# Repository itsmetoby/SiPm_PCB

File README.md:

View this project on [CADLAB.io](https://cadlab.io/project/28530). 

# SiPm_PCB

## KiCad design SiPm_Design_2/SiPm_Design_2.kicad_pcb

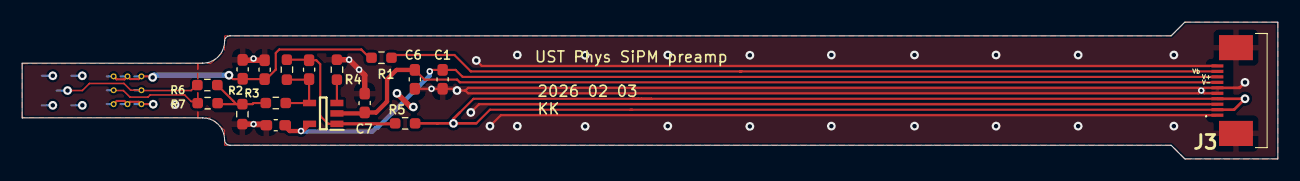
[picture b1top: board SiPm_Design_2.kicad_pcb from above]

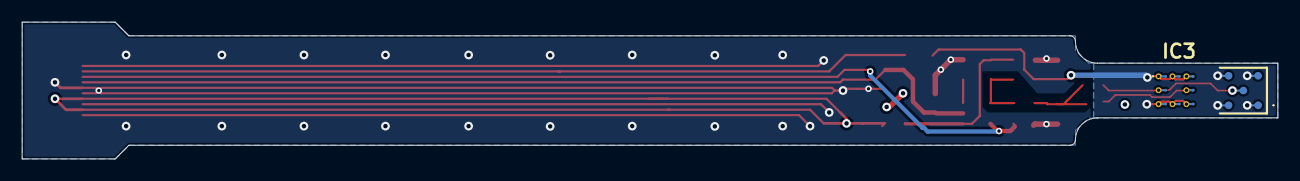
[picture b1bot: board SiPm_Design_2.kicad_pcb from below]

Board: 2 copper layers, 114.8 x 12.5 mm, 19 parts (2 on the bottom side), 12 nets.

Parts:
C1, C6: 100n; C_0603_1608Metric_Pad1.08x0.95mm_HandSolder
C2, C5, C7: 10n; C_0603_1608Metric_Pad1.08x0.95mm_HandSolder
C3: 1n; C_0603_1608Metric_Pad1.08x0.95mm_HandSolder
Cf1: 10p; C_0603_1608Metric_Pad1.08x0.95mm_HandSolder
IC1: OPA354AIDBVTG4; SOT95P280X145-5N
IC2: AFBR-S4N44P014M; AFBRS4N44P014M
IC3: MICROFJ-30035-TSV-TR; MICROFJ30035TSVTR
J3: 1-1734839-0; 117348390
R1: 1k; R_0603_1608Metric_Pad0.98x0.95mm_HandSolder
R2, R5: 50; R_0603_1608Metric_Pad0.98x0.95mm_HandSolder
R3, R4: 20; R_0603_1608Metric_Pad0.98x0.95mm_HandSolder
R6, R7: 0; R_0603_1608Metric_Pad0.98x0.95mm_HandSolder
Rf1: 200; R_0603_1608Metric_Pad0.98x0.95mm_HandSolder

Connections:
0: C1.2, C2.2, C3.2, C5.2, C6.1, C7.1, J3.1, J3.3, J3.5, J3.6, J3.10, J3.MP1, J3.MP2, R2.2, R4.2
+2V5: C1.1, C5.1, IC1.5 (V+), J3.8
-2V5: C6.2, C7.2, IC1.2 (V-), J3.7
/Bias: C2.1, C3.1, IC2.A1 (CATHODE_1), IC2.A3 (CATHODE_2), IC2.C1 (CATHODE_3), IC2.C3 (CATHODE_4), IC3.A1 (CATHODE_1), IC3.A2 (NO_CONNECT_1), IC3.A3 (NO_CONNECT_2), IC3.C1 (NO_CONNECT_3), IC3.C2 (NO_CONNECT_4), IC3.C3 (CATHODE_2), R1.1
/IN_n: Cf1.1, IC1.4 (-IN), R3.1, Rf1.1
/IN_p: IC1.3 (+IN), R4.1
/Vout: Cf1.2, IC1.1 (OUT), R5.2, Rf1.2
/anode: IC2.B2 (ANODE), IC3.B1 (ANODE), R6.1
/fastA: IC3.B3 (FAST_OUTPUT), R7.2
/in: R2.1, R3.2, R6.2, R7.1
V_bias: J3.9, R1.2
out: J3.2, J3.4, R5.1

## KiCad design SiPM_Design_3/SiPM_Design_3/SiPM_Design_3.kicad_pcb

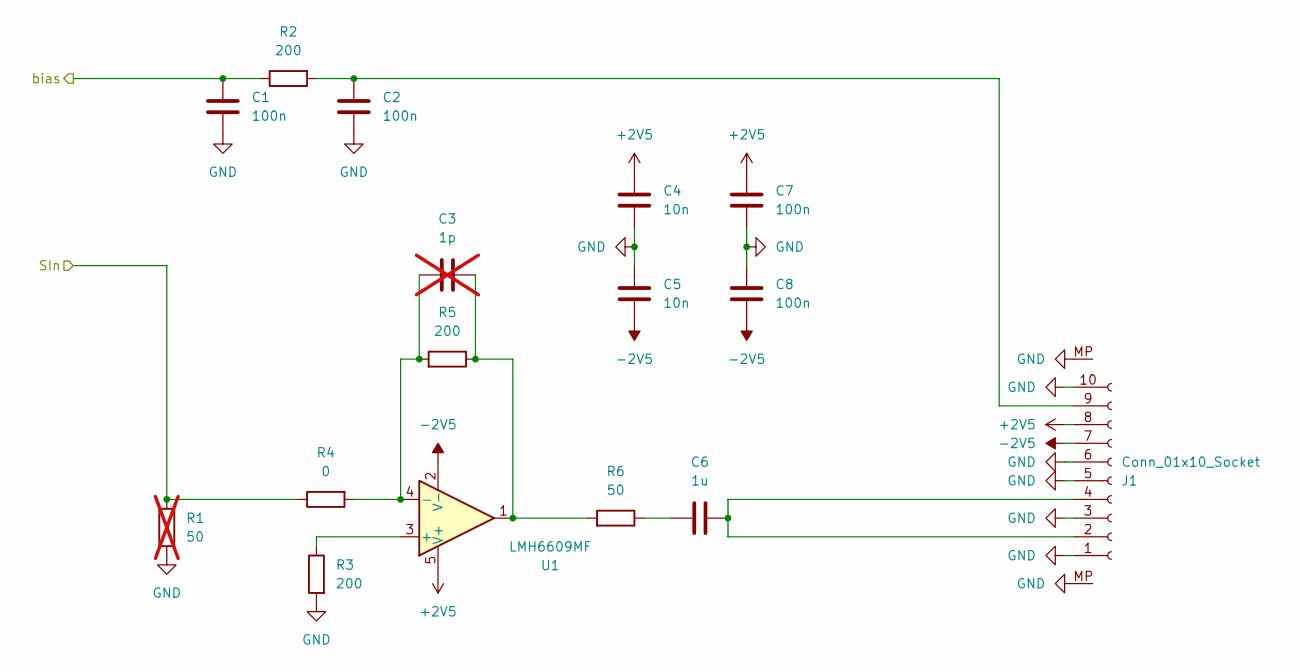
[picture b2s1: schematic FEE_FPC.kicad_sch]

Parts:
C1, C2, C7, C8: 100n; C_0603_1608Metric
C3: 1p; C_0402_1005Metric; not fitted
C4, C5: 10n; C_0402_1005Metric
C6: 1u; C_0603_1608Metric
J1: Conn_01x10_Socket; Hirose_FH12-10S-0.5SH_1x10-1MP_P0.50mm_Horizontal
R1: 50; R_0603_1608Metric; not fitted
R2, R3, R5: 200; R_0603_1608Metric
R4: 0; R_0603_1608Metric
R6: 50; R_0603_1608Metric
U1: LMH6609MF; SOT-23-5

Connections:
+2V5: C4.1, C7.1, J1.8, U1.5 (V+); also elsewhere on the board
-2V5: C5.2, C8.2, J1.7, U1.2 (V-); also elsewhere on the board
/FEE_FPC_1/SIn: R1.2, R4.2; also elsewhere on the board
/SiPM_onsemi/C: C1.1, R2.2; also elsewhere on the board
GND: C1.2, C2.2, C4.2, C5.1, C7.2, C8.1, J1.1, J1.3, J1.5, J1.6, J1.10, J1.MP, R1.1, R3.1; also elsewhere on the board
unnamed: C3.2, R5.2, R6.1, U1.1
unnamed: C6.1, R6.2
unnamed: C6.2, J1.2, J1.4
unnamed: C2.1, J1.9, R2.1
unnamed: R3.2, U1.3 (+)
unnamed: C3.1, R4.1, R5.1, U1.4 (-)

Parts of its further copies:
C9, C10, C15, C16: 100n; C_0603_1608Metric
C11: 1p; C_0402_1005Metric; not fitted
C12, C13: 10n; C_0402_1005Metric
C14: 1u; C_0603_1608Metric
J2: Conn_01x10_Socket; Hirose_FH12-10S-0.5SH_1x10-1MP_P0.50mm_Horizontal
R7: 50; R_0603_1608Metric; not fitted
R8, R9, R11: 200; R_0603_1608Metric
R10: 0; R_0603_1608Metric
R12: 50; R_0603_1608Metric
U2: LMH6609MF; SOT-23-5

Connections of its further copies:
+2V5: C12.1, C15.1, J2.8, U2.5 (V+); also elsewhere on the board
-2V5: C13.2, C16.2, J2.7, U2.2 (V-); also elsewhere on the board
/SiPM_broadcom/A: R7.2, R10.2; also elsewhere on the board
/SiPM_broadcom/C: C9.1, R8.2; also elsewhere on the board
GND: C9.2, C10.2, C12.2, C13.1, C15.2, C16.1, J2.1, J2.3, J2.5, J2.6, J2.10, J2.MP, R7.1, R9.1; also elsewhere on the board
unnamed: C11.2, R11.2, R12.1, U2.1
unnamed: C14.1, R12.2
unnamed: C14.2, J2.2, J2.4
unnamed: C10.1, J2.9, R8.1
unnamed: R9.2, U2.3 (+)
unnamed: C11.1, R10.1, R11.1, U2.4 (-)

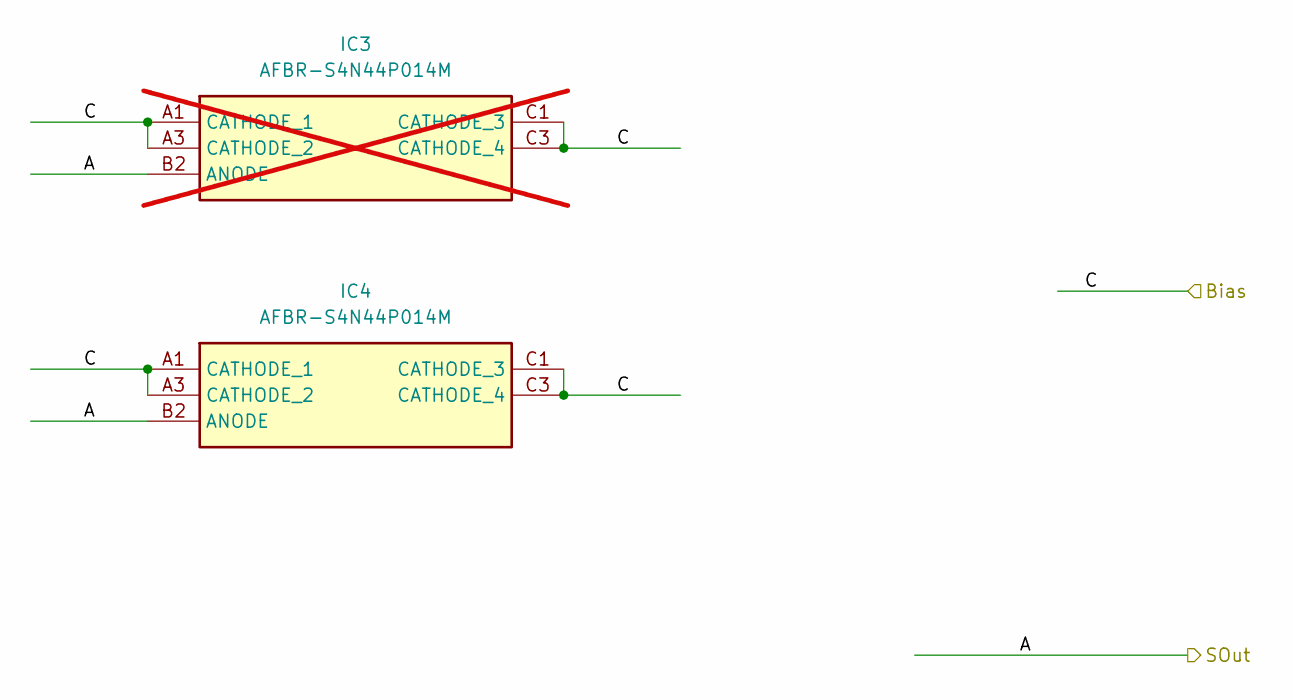
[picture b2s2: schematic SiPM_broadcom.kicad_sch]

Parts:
IC3: AFBR-S4N44P014M; AFBRS4N44P014M_offset; Manufacturer_Part_Number AFBR-S4N44P014M; Mouser Part Number 630-AFBR-S4N44P014M; not fitted
IC4: AFBR-S4N44P014M; AFBRS4N44P014M_offset; Manufacturer_Part_Number AFBR-S4N44P014M; Mouser Part Number 630-AFBR-S4N44P014M

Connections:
/SiPM_broadcom/A: IC3.B2 (ANODE), IC4.B2 (ANODE); also elsewhere on the board
/SiPM_broadcom/C: IC3.A1 (CATHODE_1), IC3.A3 (CATHODE_2), IC3.C1 (CATHODE_3), IC3.C3 (CATHODE_4), IC4.A1 (CATHODE_1), IC4.A3 (CATHODE_2), IC4.C1 (CATHODE_3), IC4.C3 (CATHODE_4); also elsewhere on the board

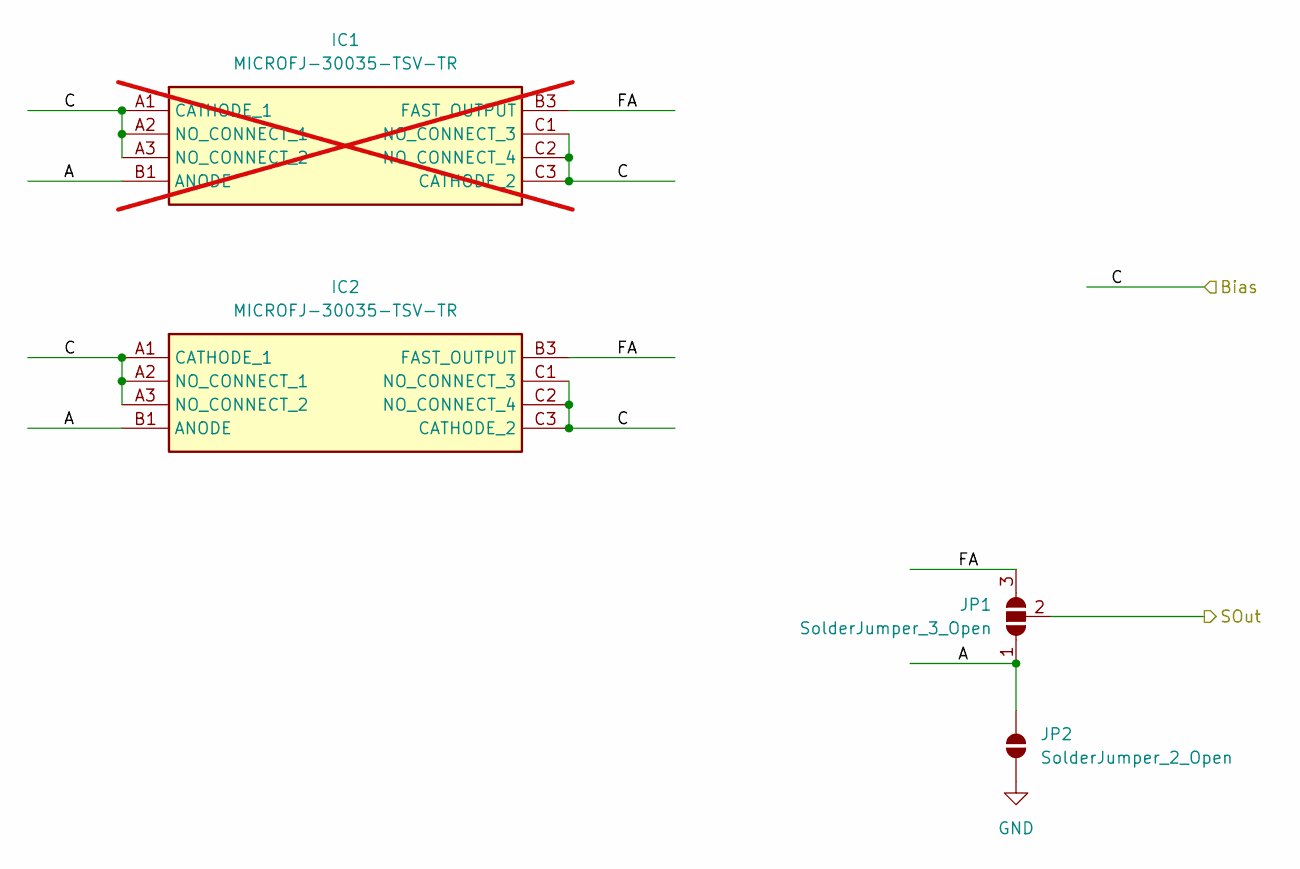
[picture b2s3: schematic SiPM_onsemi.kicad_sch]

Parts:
IC1: MICROFJ-30035-TSV-TR; MICROFJ30035TSVTR_offset; Manufacturer_Part_Number MICROFJ-30035-TSV-TR; Mouser Part Number 863-MFJ30035TSVTR; not fitted
IC2: MICROFJ-30035-TSV-TR; MICROFJ30035TSVTR_offset; Manufacturer_Part_Number MICROFJ-30035-TSV-TR; Mouser Part Number 863-MFJ30035TSVTR
JP1: SolderJumper_3_Open; SolderJumper-3_P1.3mm_Open_Pad1.0x1.5mm
JP2: SolderJumper_2_Open; SolderJumper-2_P1.3mm_Open_RoundedPad1.0x1.5mm

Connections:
/FEE_FPC_1/SIn: JP1.2 (C); also elsewhere on the board
/SiPM_onsemi/A: IC1.B1 (ANODE), IC2.B1 (ANODE), JP1.1 (A), JP2.2 (B)
/SiPM_onsemi/C: IC1.A1 (CATHODE_1), IC1.A2 (NO_CONNECT_1), IC1.A3 (NO_CONNECT_2), IC1.C1 (NO_CONNECT_3), IC1.C2 (NO_CONNECT_4), IC1.C3 (CATHODE_2), IC2.A1 (CATHODE_1), IC2.A2 (NO_CONNECT_1), IC2.A3 (NO_CONNECT_2), IC2.C1 (NO_CONNECT_3), IC2.C2 (NO_CONNECT_4), IC2.C3 (CATHODE_2); also elsewhere on the board
/SiPM_onsemi/FA: IC1.B3 (FAST_OUTPUT), IC2.B3 (FAST_OUTPUT), JP1.3 (B)
GND: JP2.1 (A); also elsewhere on the board

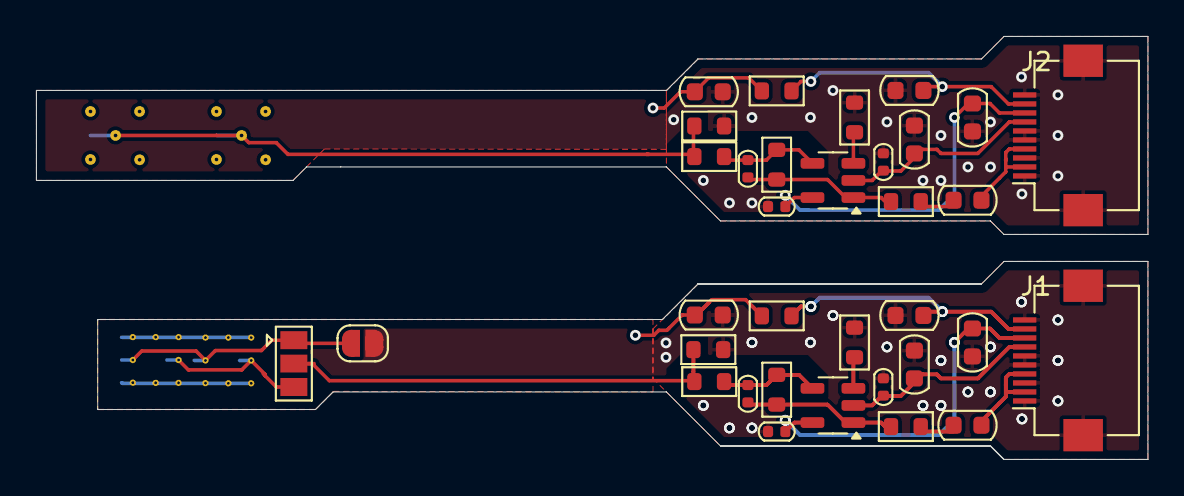
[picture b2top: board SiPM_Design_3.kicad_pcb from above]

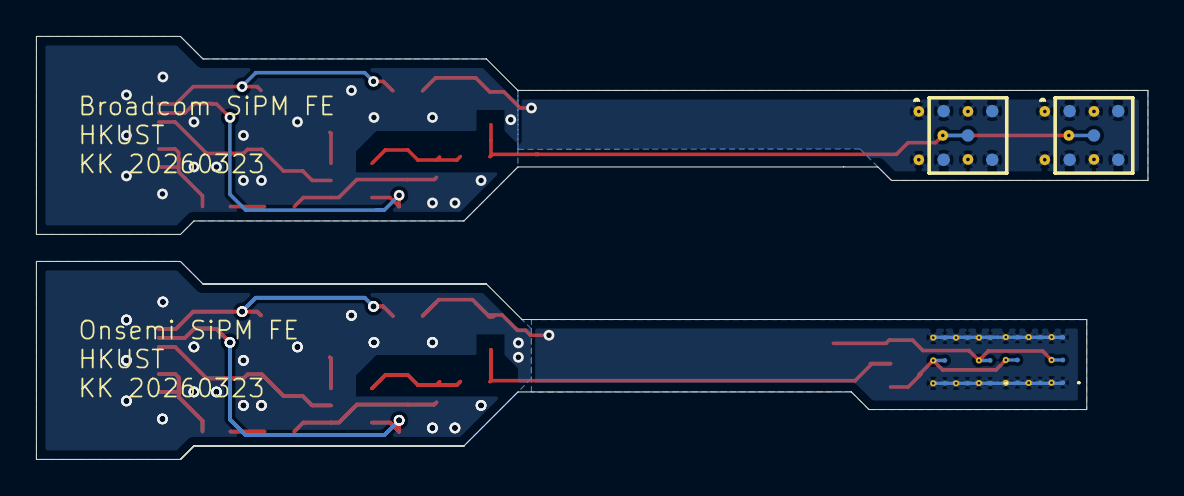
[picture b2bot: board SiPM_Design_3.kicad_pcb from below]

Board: 2 copper layers, 61.8 x 23.5 mm, 38 parts (4 on the bottom side), 21 nets.

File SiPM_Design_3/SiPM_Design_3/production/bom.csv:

Designator,Footprint,Quantity,Value,LCSC Part #
"C1, C10, C15, C16, C2, C7, C8, C9",0603,8,100n,
"C12, C13, C4, C5",0402,4,10n,
"C14, C6",0603,2,1u,
IC2,MICROFJ30035TSVTR_offset,1,MICROFJ-30035-TSV-TR,
IC4,AFBRS4N44P014M_offset,1,AFBR-S4N44P014M,
"J1, J2",Hirose_FH12-10S-0.5SH_1x10-1MP_P0.50mm_Horizontal,2,Conn_01x10_Socket,
"R10, R4",0603,2,0,
"R11, R2, R3, R5, R8, R9",0603,6,200,
"R12, R6",0603,2,50,
"U1, U2",SOT-23-5,2,LMH6609MF,

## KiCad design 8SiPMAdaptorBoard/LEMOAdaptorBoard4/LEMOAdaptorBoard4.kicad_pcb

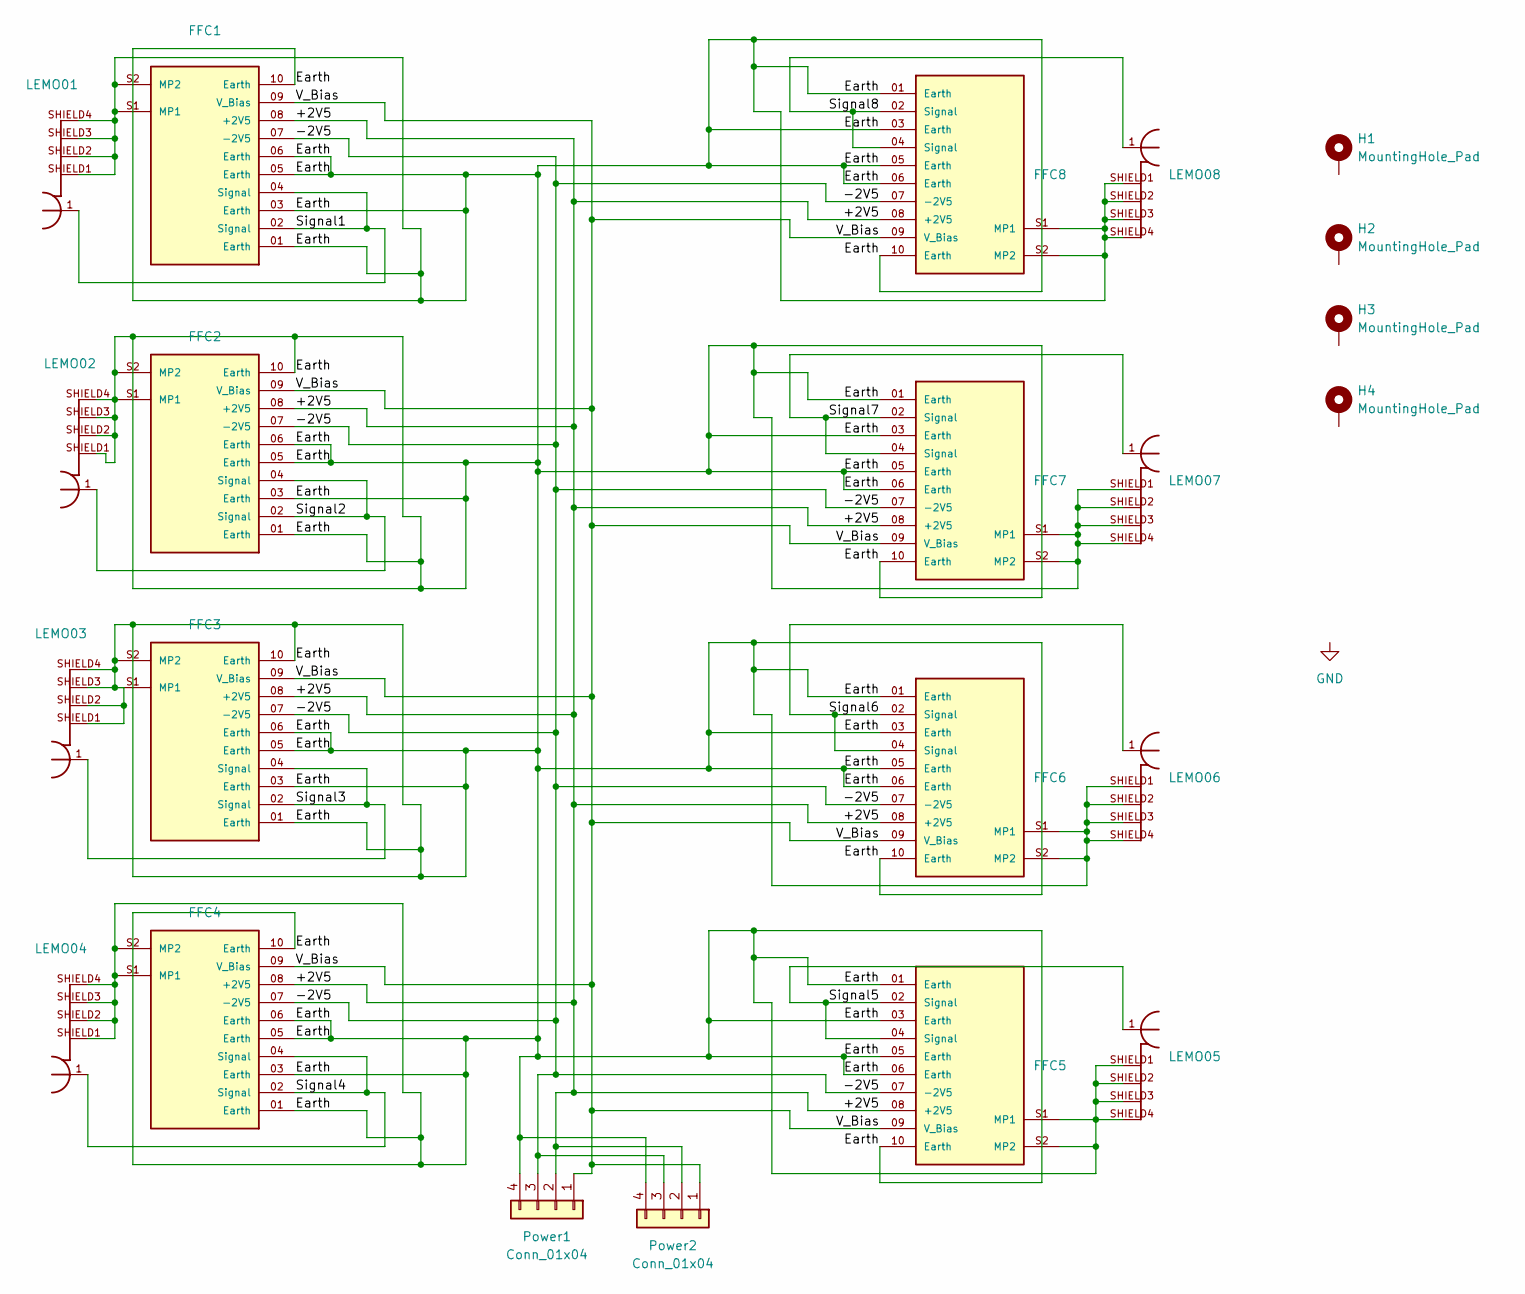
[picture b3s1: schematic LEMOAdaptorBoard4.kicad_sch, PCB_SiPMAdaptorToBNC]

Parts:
FFC1, FFC2, FFC3, FFC4, FFC5, FFC6, FFC7, FFC8: FFC_Connector_Vertical; SAMTEC_ZF5S-10-01-T-WT
H1, H2, H3, H4: MountingHole_Pad; MountingHole_5mm_Pad
LEMO01, LEMO02, LEMO03, LEMO04, LEMO05, LEMO06, LEMO07, LEMO08: FPL.00.250.NTD
Power1, Power2: Conn_01x04; PinHeader_1x04_P2.54mm_Horizontal

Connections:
/+2V5: FFC1.08 (+2V5), FFC2.08 (+2V5), FFC3.08 (+2V5), FFC4.08 (+2V5), FFC5.08 (+2V5), FFC6.08 (+2V5), FFC7.08 (+2V5), FFC8.08 (+2V5), Power1.2, Power2.2
/-2V5: FFC1.07 (-2V5), FFC2.07 (-2V5), FFC3.07 (-2V5), FFC4.07 (-2V5), FFC5.07 (-2V5), FFC6.07 (-2V5), FFC7.07 (-2V5), FFC8.07 (-2V5), Power1.3, Power2.3
/Earth: FFC1.01 (Earth), FFC1.03 (Earth), FFC1.05 (Earth), FFC1.06 (Earth), FFC1.10 (Earth), FFC1.S1 (MP1), FFC1.S2 (MP2), FFC2.01 (Earth), FFC2.03 (Earth), FFC2.05 (Earth), FFC2.06 (Earth), FFC2.10 (Earth), FFC2.S1 (MP1), FFC2.S2 (MP2), FFC3.01 (Earth), FFC3.03 (Earth), FFC3.05 (Earth), FFC3.06 (Earth), FFC3.10 (Earth), FFC3.S1 (MP1), FFC3.S2 (MP2), FFC4.01 (Earth), FFC4.03 (Earth), FFC4.05 (Earth), FFC4.06 (Earth), FFC4.10 (Earth), FFC4.S1 (MP1), FFC4.S2 (MP2), FFC5.01 (Earth), FFC5.03 (Earth), FFC5.05 (Earth), FFC5.06 (Earth), FFC5.10 (Earth), FFC5.S1 (MP1), FFC5.S2 (MP2), FFC6.01 (Earth), FFC6.03 (Earth), FFC6.05 (Earth), FFC6.06 (Earth), FFC6.10 (Earth), FFC6.S1 (MP1), FFC6.S2 (MP2), FFC7.01 (Earth), FFC7.03 (Earth), FFC7.05 (Earth), FFC7.06 (Earth), FFC7.10 (Earth), FFC7.S1 (MP1), FFC7.S2 (MP2), FFC8.01 (Earth), FFC8.03 (Earth), FFC8.05 (Earth), FFC8.06 (Earth), FFC8.10 (Earth), FFC8.S1 (MP1), FFC8.S2 (MP2), LEMO01.SHIELD1, LEMO01.SHIELD2, LEMO01.SHIELD3, LEMO01.SHIELD4, LEMO02.SHIELD1, LEMO02.SHIELD2, LEMO02.SHIELD3, LEMO02.SHIELD4, LEMO03.SHIELD1, LEMO03.SHIELD2, LEMO03.SHIELD3, LEMO03.SHIELD4, LEMO04.SHIELD1, LEMO04.SHIELD2, LEMO04.SHIELD3, LEMO04.SHIELD4, LEMO05.SHIELD1, LEMO05.SHIELD2, LEMO05.SHIELD3, LEMO05.SHIELD4, LEMO06.SHIELD1, LEMO06.SHIELD2, LEMO06.SHIELD3, LEMO06.SHIELD4, LEMO07.SHIELD1, LEMO07.SHIELD2, LEMO07.SHIELD3, LEMO07.SHIELD4, LEMO08.SHIELD1, LEMO08.SHIELD2, LEMO08.SHIELD3, LEMO08.SHIELD4, Power1.4, Power2.4
/Signal1: FFC1.02 (Signal), FFC1.04 (Signal), LEMO01.1
/Signal2: FFC2.02 (Signal), FFC2.04 (Signal), LEMO02.1
/Signal3: FFC3.02 (Signal), FFC3.04 (Signal), LEMO03.1
/Signal4: FFC4.02 (Signal), FFC4.04 (Signal), LEMO04.1
/Signal5: FFC5.02 (Signal), FFC5.04 (Signal), LEMO05.1
/Signal6: FFC6.02 (Signal), FFC6.04 (Signal), LEMO06.1
/Signal7: FFC7.02 (Signal), FFC7.04 (Signal), LEMO07.1
/Signal8: FFC8.02 (Signal), FFC8.04 (Signal), LEMO08.1
/V_Bias: FFC1.09 (V_Bias), FFC2.09 (V_Bias), FFC3.09 (V_Bias), FFC4.09 (V_Bias), FFC5.09 (V_Bias), FFC6.09 (V_Bias), FFC7.09 (V_Bias), FFC8.09 (V_Bias), Power1.1, Power2.1

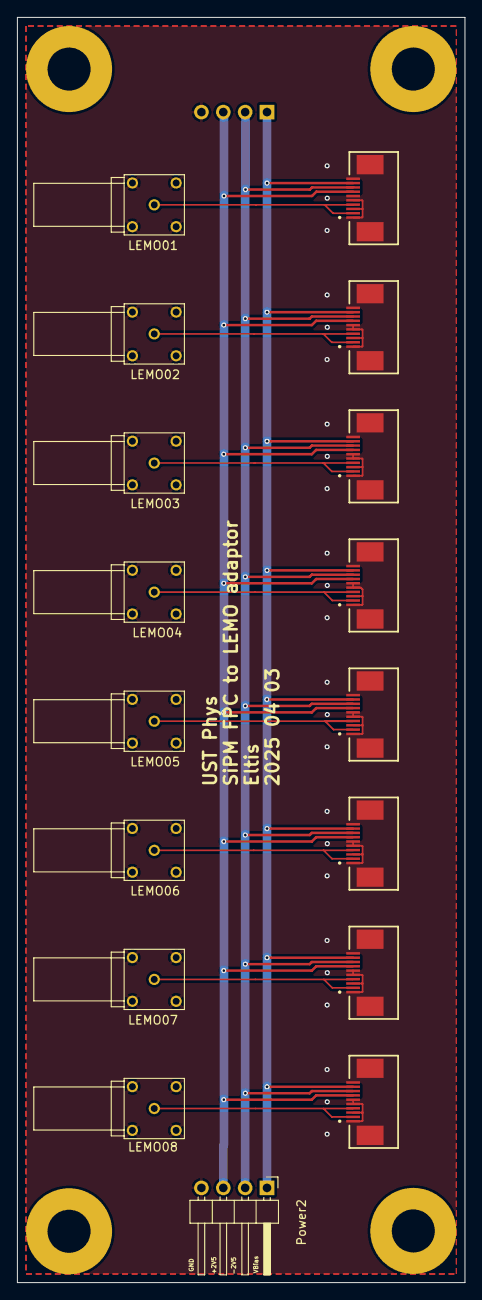
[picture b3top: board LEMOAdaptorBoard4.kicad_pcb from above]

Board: 2 copper layers, 52.0 x 147.0 mm, 22 parts (1 on the bottom side), 12 nets.

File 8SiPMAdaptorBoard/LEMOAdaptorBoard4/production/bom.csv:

Designator,Footprint,Quantity,Value,LCSC Part #
"FFC1, FFC2, FFC3, FFC4, FFC5, FFC6, FFC7, FFC8",SAMTEC_ZF5S-10-01-T-WT,8,FFC_Connector_Vertical,
"LEMO01, LEMO02, LEMO03, LEMO04, LEMO05, LEMO06, LEMO07, LEMO08",FPL.00.250.NTD,8,FPL.00.250.NTD,
"POWER1, POWER2",PinHeader_1x04_P2.54mm_Horizontal,2,Conn_01x04,

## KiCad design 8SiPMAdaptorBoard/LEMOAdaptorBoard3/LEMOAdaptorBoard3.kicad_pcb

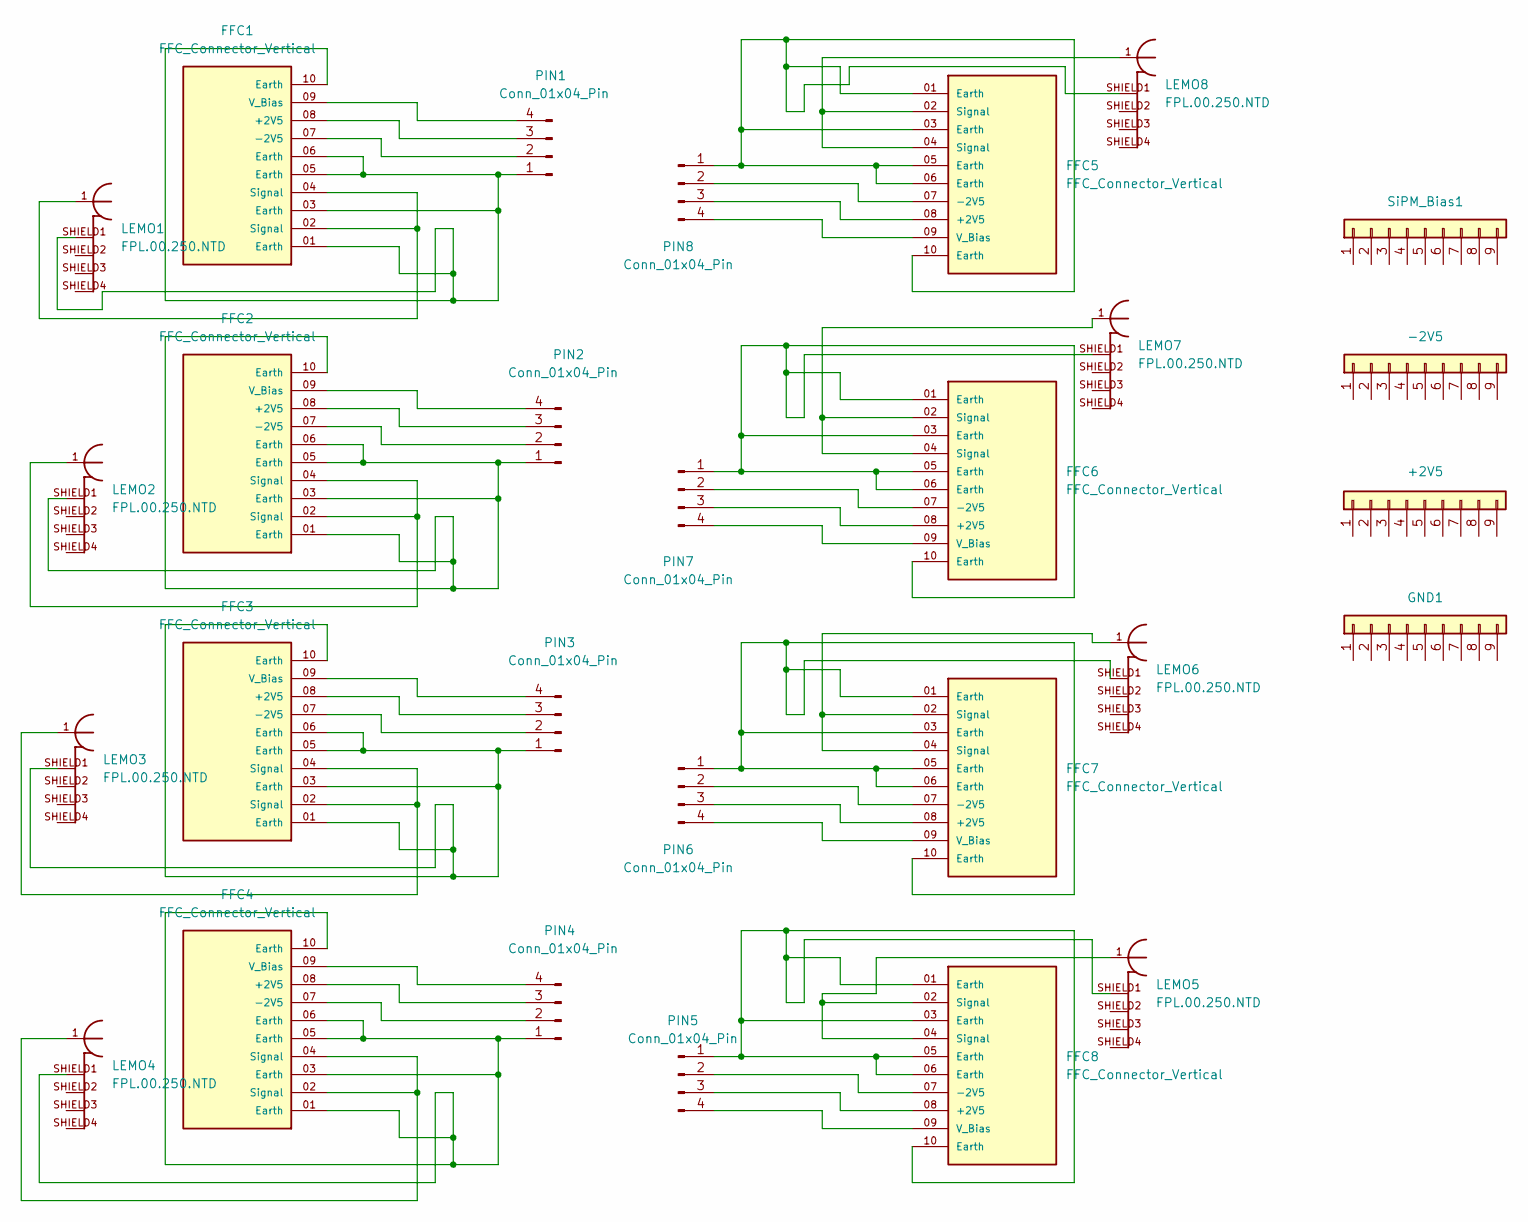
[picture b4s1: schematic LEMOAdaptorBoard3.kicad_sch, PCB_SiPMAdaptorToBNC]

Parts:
+2V5: Conn_01x09; PinHeader_1x09_P1.00mm_Vertical
-2V5: Conn_01x09; PinHeader_1x09_P1.00mm_Vertical
FFC1, FFC2, FFC3, FFC4, FFC5, FFC6, FFC7, FFC8: FFC_Connector_Vertical; SAMTEC_ZF5S-10-01-T-WT
GND1: Conn_01x09; PinHeader_1x09_P1.00mm_Vertical
LEMO1, LEMO2, LEMO3, LEMO4, LEMO5, LEMO6, LEMO7, LEMO8: FPL.00.250.NTD
PIN1, PIN2, PIN3, PIN4, PIN5, PIN6, PIN7, PIN8: Conn_01x04_Pin; PinHeader_1x04_P1.00mm_Vertical
SiPM_Bias1: Conn_01x09; PinHeader_1x09_P1.00mm_Vertical

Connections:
unnamed: FFC1.08 (+2V5), PIN1.3
unnamed: FFC1.07 (-2V5), PIN1.2
unnamed: FFC1.02 (Signal), FFC1.04 (Signal), LEMO1.1
unnamed: FFC1.09 (V_Bias), PIN1.4
unnamed: FFC2.08 (+2V5), PIN2.3
unnamed: FFC2.07 (-2V5), PIN2.2
unnamed: FFC2.02 (Signal), FFC2.04 (Signal), LEMO2.1
unnamed: FFC2.09 (V_Bias), PIN2.4
unnamed: FFC3.08 (+2V5), PIN3.3
unnamed: FFC3.07 (-2V5), PIN3.2
unnamed: FFC3.02 (Signal), FFC3.04 (Signal), LEMO3.1
unnamed: FFC3.09 (V_Bias), PIN3.4
unnamed: FFC4.08 (+2V5), PIN4.3
unnamed: FFC4.07 (-2V5), PIN4.2
unnamed: FFC4.02 (Signal), FFC4.04 (Signal), LEMO4.1
unnamed: FFC4.09 (V_Bias), PIN4.4
unnamed: FFC5.08 (+2V5), PIN8.3
unnamed: FFC5.07 (-2V5), PIN8.2
unnamed: FFC5.02 (Signal), FFC5.04 (Signal), LEMO8.1
unnamed: FFC5.09 (V_Bias), PIN8.4
unnamed: FFC6.08 (+2V5), PIN7.3
unnamed: FFC6.07 (-2V5), PIN7.2
unnamed: FFC6.02 (Signal), FFC6.04 (Signal), LEMO7.1
unnamed: FFC6.09 (V_Bias), PIN7.4
unnamed: FFC7.08 (+2V5), PIN6.3
unnamed: FFC7.07 (-2V5), PIN6.2
unnamed: FFC7.02 (Signal), FFC7.04 (Signal), LEMO6.1
unnamed: FFC7.09 (V_Bias), PIN6.4
unnamed: FFC8.08 (+2V5), PIN5.3
unnamed: FFC8.07 (-2V5), PIN5.2
unnamed: FFC8.02 (Signal), FFC8.04 (Signal), LEMO5.1
unnamed: FFC8.09 (V_Bias), PIN5.4
unnamed: FFC1.01 (Earth), FFC1.03 (Earth), FFC1.05 (Earth), FFC1.06 (Earth), FFC1.10 (Earth), LEMO1.SHIELD1, PIN1.1
unnamed: FFC2.01 (Earth), FFC2.03 (Earth), FFC2.05 (Earth), FFC2.06 (Earth), FFC2.10 (Earth), LEMO2.SHIELD1, PIN2.1
unnamed: FFC3.01 (Earth), FFC3.03 (Earth), FFC3.05 (Earth), FFC3.06 (Earth), FFC3.10 (Earth), LEMO3.SHIELD1, PIN3.1
unnamed: FFC4.01 (Earth), FFC4.03 (Earth), FFC4.05 (Earth), FFC4.06 (Earth), FFC4.10 (Earth), LEMO4.SHIELD1, PIN4.1
unnamed: FFC8.01 (Earth), FFC8.03 (Earth), FFC8.05 (Earth), FFC8.06 (Earth), FFC8.10 (Earth), LEMO5.SHIELD1, PIN5.1
unnamed: FFC7.01 (Earth), FFC7.03 (Earth), FFC7.05 (Earth), FFC7.06 (Earth), FFC7.10 (Earth), LEMO6.SHIELD1, PIN6.1
unnamed: FFC6.01 (Earth), FFC6.03 (Earth), FFC6.05 (Earth), FFC6.06 (Earth), FFC6.10 (Earth), LEMO7.SHIELD1, PIN7.1
unnamed: FFC5.01 (Earth), FFC5.03 (Earth), FFC5.05 (Earth), FFC5.06 (Earth), FFC5.10 (Earth), LEMO8.SHIELD1, PIN8.1

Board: 2 copper layers, 28 parts (0 on the bottom side), 40 nets, no tracks yet.

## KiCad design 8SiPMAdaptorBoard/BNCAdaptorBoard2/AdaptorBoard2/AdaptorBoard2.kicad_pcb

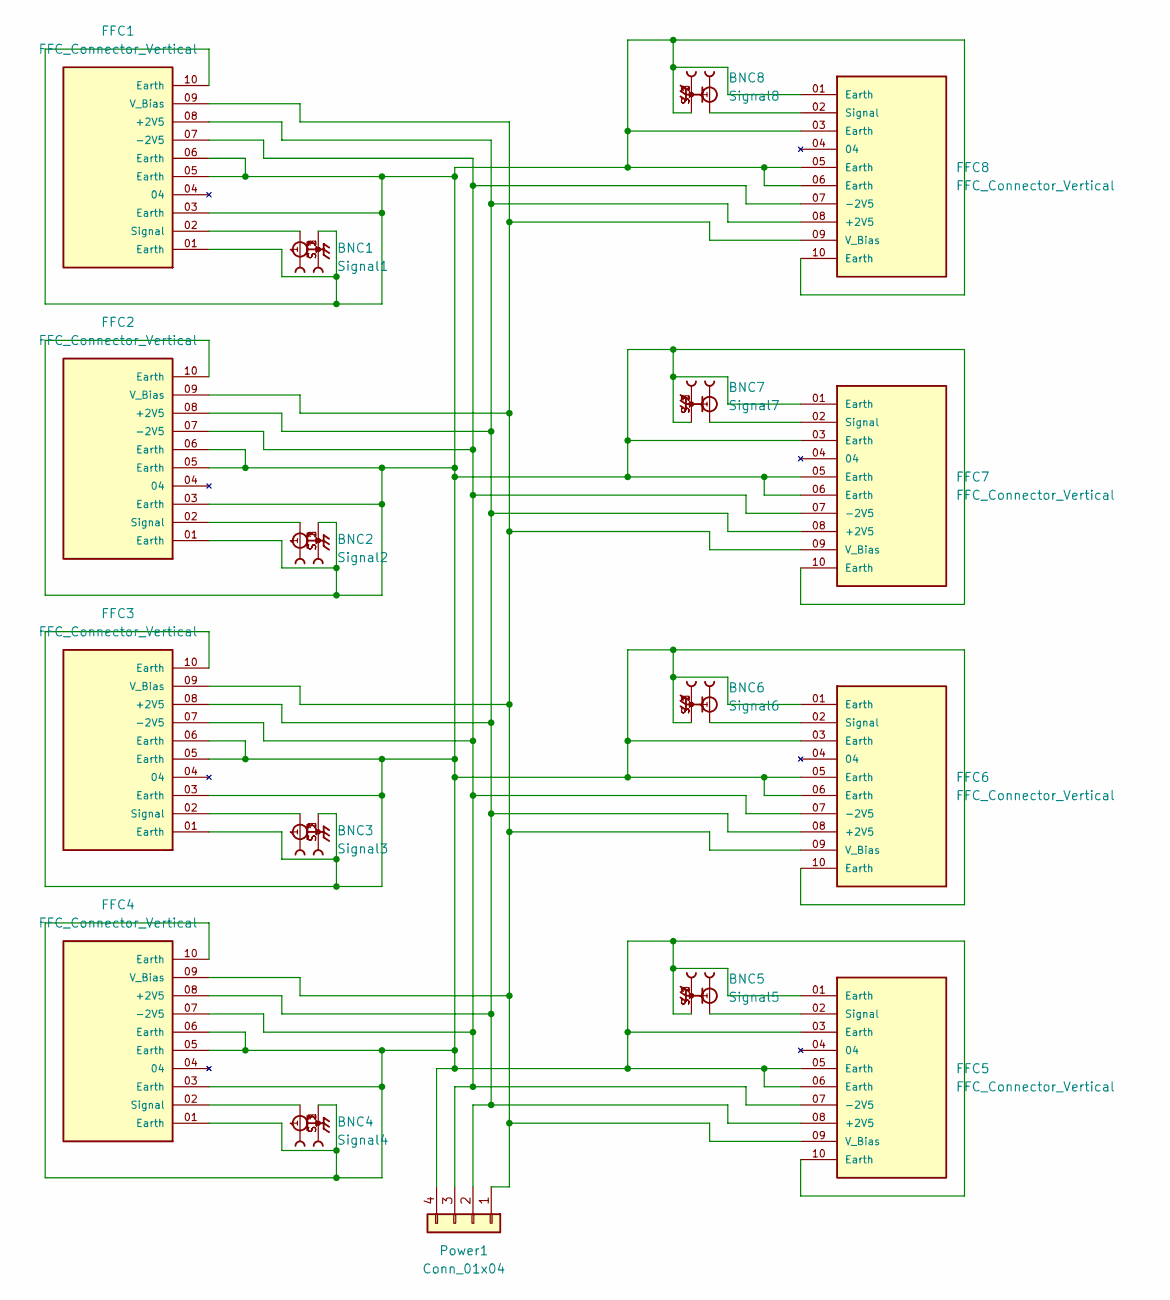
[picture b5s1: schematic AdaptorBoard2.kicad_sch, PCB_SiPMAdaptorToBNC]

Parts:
BNC1: Signal1; SAMTEC_BNC5-J-P-GN-ST-TH2D
BNC2: Signal2; SAMTEC_BNC5-J-P-GN-ST-TH2D
BNC3: Signal3; SAMTEC_BNC5-J-P-GN-ST-TH2D
BNC4: Signal4; SAMTEC_BNC5-J-P-GN-ST-TH2D
BNC5: Signal5; SAMTEC_BNC5-J-P-GN-ST-TH2D
BNC6: Signal6; SAMTEC_BNC5-J-P-GN-ST-TH2D
BNC7: Signal7; SAMTEC_BNC5-J-P-GN-ST-TH2D
BNC8: Signal8; SAMTEC_BNC5-J-P-GN-ST-TH2D
FFC1, FFC2, FFC3, FFC4, FFC5, FFC6, FFC7, FFC8: FFC_Connector_Vertical; SAMTEC_ZF5S-10-03-T-WT
Power1: Conn_01x04; PinHeader_1x04_P1.00mm_Vertical

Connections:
unnamed: FFC1.08 (+2V5), FFC2.08 (+2V5), FFC3.08 (+2V5), FFC4.08 (+2V5), FFC5.08 (+2V5), FFC6.08 (+2V5), FFC7.08 (+2V5), FFC8.08 (+2V5), Power1.2
unnamed: FFC1.07 (-2V5), FFC2.07 (-2V5), FFC3.07 (-2V5), FFC4.07 (-2V5), FFC5.07 (-2V5), FFC6.07 (-2V5), FFC7.07 (-2V5), FFC8.07 (-2V5), Power1.3
unnamed: BNC1.1, FFC1.02 (Signal)
unnamed: FFC1.09 (V_Bias), FFC2.09 (V_Bias), FFC3.09 (V_Bias), FFC4.09 (V_Bias), FFC5.09 (V_Bias), FFC6.09 (V_Bias), FFC7.09 (V_Bias), FFC8.09 (V_Bias), Power1.1
unnamed: BNC2.1, FFC2.02 (Signal)
unnamed: BNC3.1, FFC3.02 (Signal)
unnamed: BNC4.1, FFC4.02 (Signal)
unnamed: BNC5.1, FFC5.02 (Signal)
unnamed: BNC6.1, FFC6.02 (Signal)
unnamed: BNC7.1, FFC7.02 (Signal)
unnamed: BNC8.1, FFC8.02 (Signal)
unnamed: BNC1.S_1, BNC1.S_2, BNC1.S_3, BNC2.S_1, BNC2.S_2, BNC2.S_3, BNC3.S_1, BNC3.S_2, BNC3.S_3, BNC4.S_1, BNC4.S_2, BNC4.S_3, BNC5.S_1, BNC5.S_2, BNC5.S_3, BNC6.S_1, BNC6.S_2, BNC6.S_3, BNC7.S_1, BNC7.S_2, BNC7.S_3, BNC8.S_1, BNC8.S_2, BNC8.S_3, FFC1.01 (Earth), FFC1.03 (Earth), FFC1.05 (Earth), FFC1.06 (Earth), FFC1.10 (Earth), FFC2.01 (Earth), FFC2.03 (Earth), FFC2.05 (Earth), FFC2.06 (Earth), FFC2.10 (Earth), FFC3.01 (Earth), FFC3.03 (Earth), FFC3.05 (Earth), FFC3.06 (Earth), FFC3.10 (Earth), FFC4.01 (Earth), FFC4.03 (Earth), FFC4.05 (Earth), FFC4.06 (Earth), FFC4.10 (Earth), FFC5.01 (Earth), FFC5.03 (Earth), FFC5.05 (Earth), FFC5.06 (Earth), FFC5.10 (Earth), FFC6.01 (Earth), FFC6.03 (Earth), FFC6.05 (Earth), FFC6.06 (Earth), FFC6.10 (Earth), FFC7.01 (Earth), FFC7.03 (Earth), FFC7.05 (Earth), FFC7.06 (Earth), FFC7.10 (Earth), FFC8.01 (Earth), FFC8.03 (Earth), FFC8.05 (Earth), FFC8.06 (Earth), FFC8.10 (Earth), Power1.4

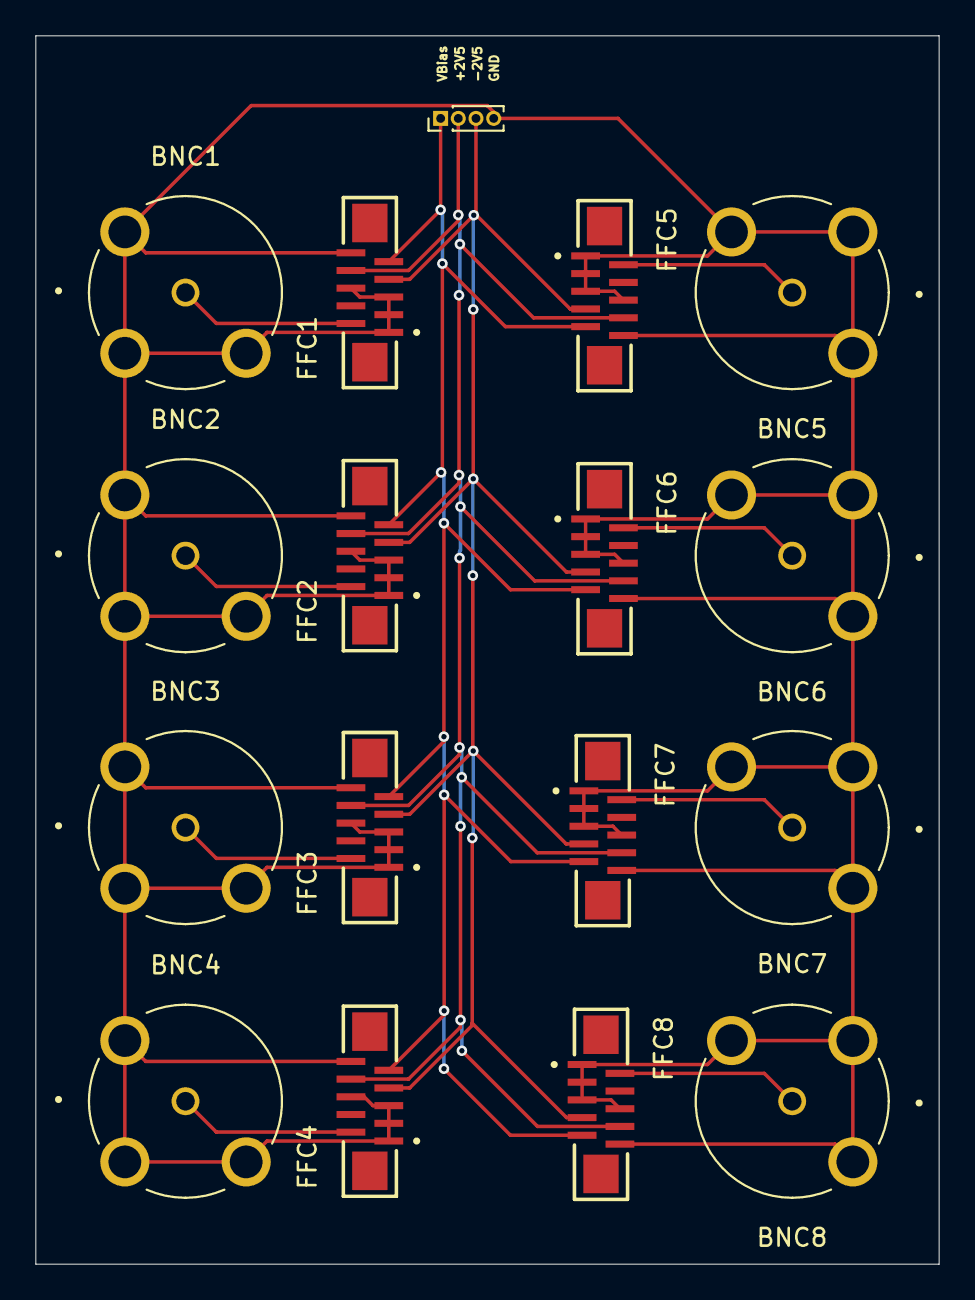
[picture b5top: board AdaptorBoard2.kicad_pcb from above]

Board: 2 copper layers, 51.1 x 69.5 mm, 17 parts (0 on the bottom side), 12 nets.
